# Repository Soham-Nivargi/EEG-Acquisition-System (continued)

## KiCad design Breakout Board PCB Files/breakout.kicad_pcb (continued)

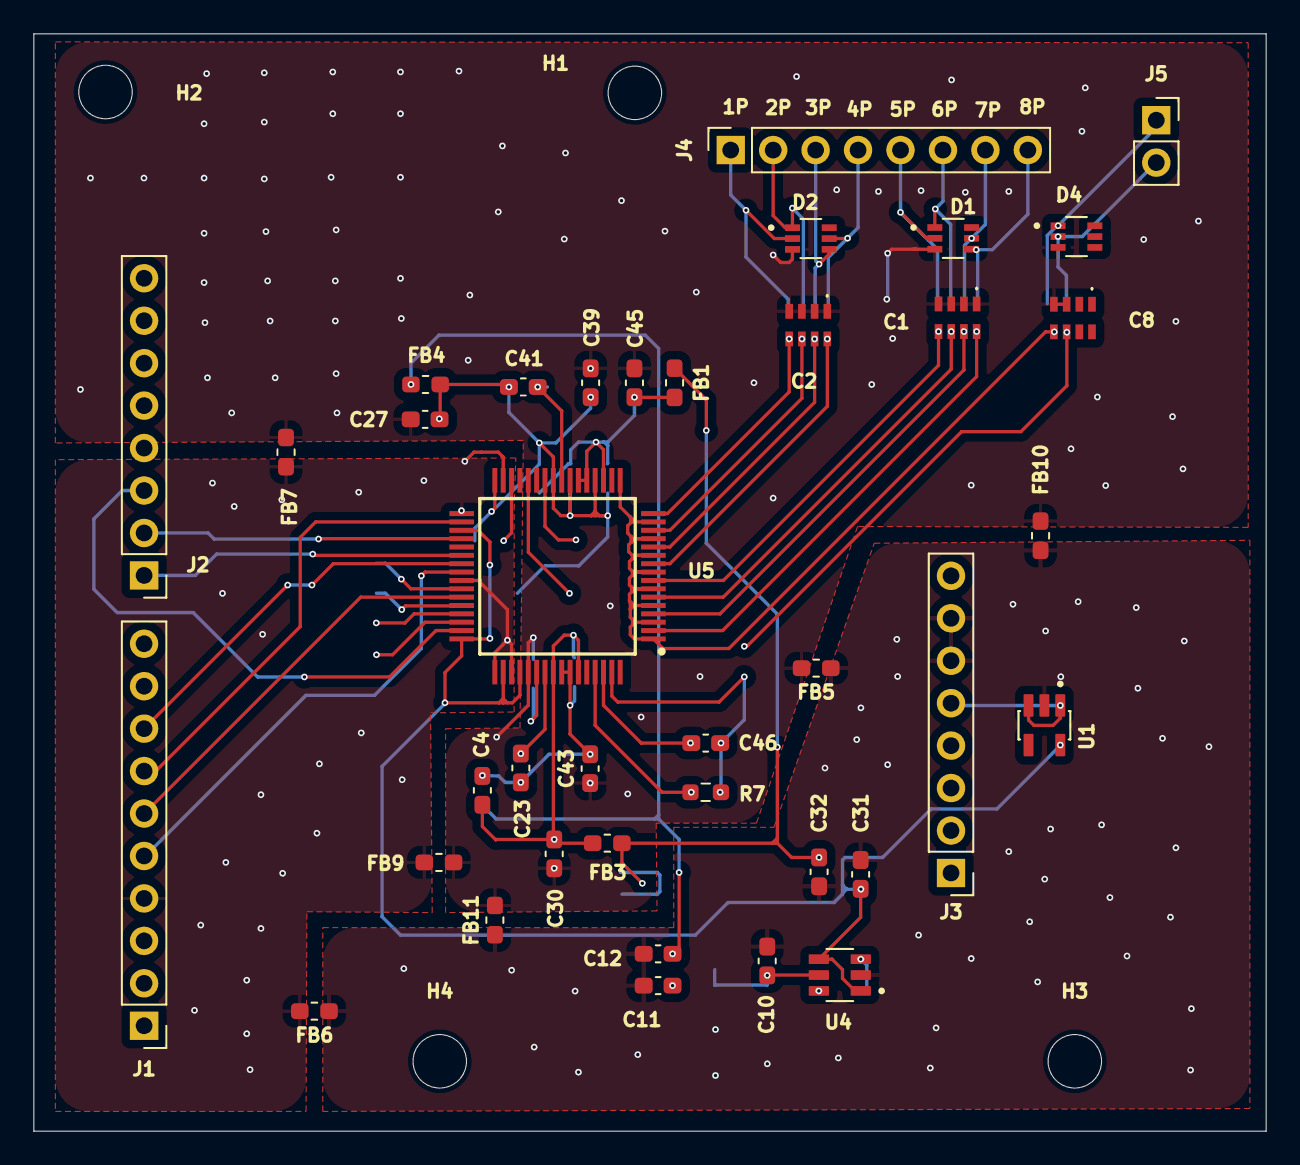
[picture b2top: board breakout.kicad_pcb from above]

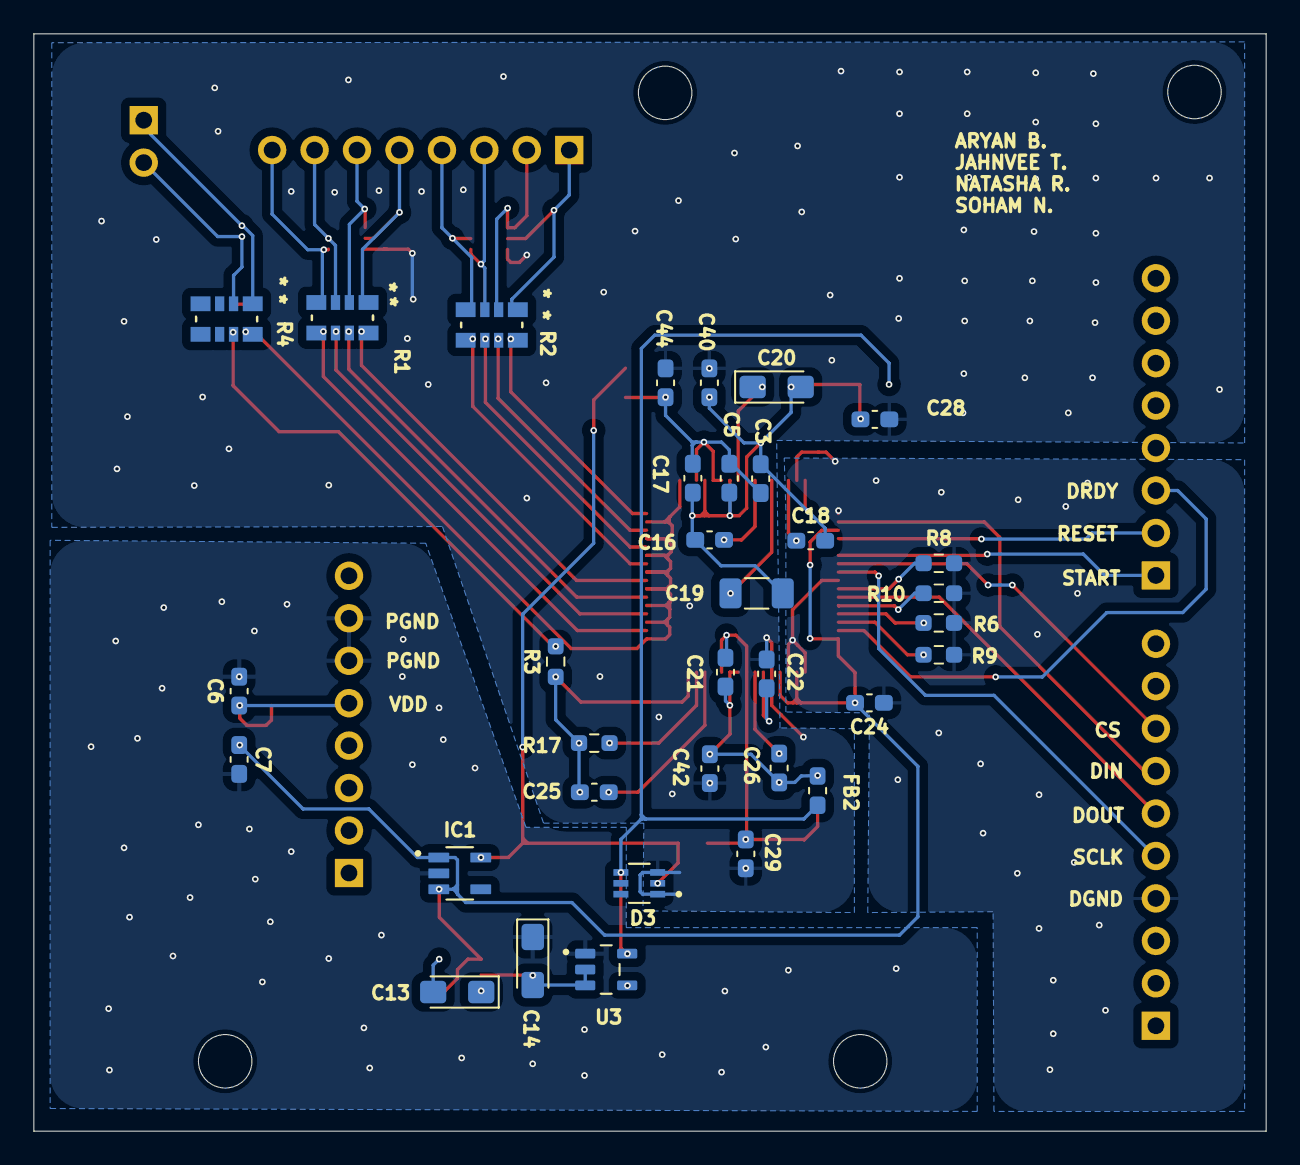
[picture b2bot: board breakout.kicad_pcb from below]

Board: 2 copper layers, 73.7 x 65.7 mm, 76 parts (34 on the bottom side), 55 nets.

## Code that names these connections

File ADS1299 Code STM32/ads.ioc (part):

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Mcu.Name=STM32F103R(8-B)Tx
Mcu.Package=LQFP64
Mcu.UserName=STM32F103RBTx
PA13.GPIOParameters=GPIO_Label
PA13.GPIO_Label=TMS
PA13.Mode=Serial_Wire
PA13.Signal=SYS_JTMS-SWDIO
PA14.GPIOParameters=GPIO_Label
PA14.GPIO_Label=TCK
PA14.Mode=Serial_Wire
PA14.Signal=SYS_JTCK-SWCLK
PA2.GPIOParameters=GPIO_Speed,GPIO_PuPd,GPIO_Label,GPIO_Mode
PA2.GPIO_Label=USART_TX
PA2.GPIO_Mode=GPIO_MODE_AF_PP
PA2.GPIO_PuPd=GPIO_NOPULL
PA2.GPIO_Speed=GPIO_SPEED_FREQ_LOW
PA2.Mode=Asynchronous
PA2.Signal=USART2_TX
PA3.GPIOParameters=GPIO_Speed,GPIO_PuPd,GPIO_Label,GPIO_Mode
PA3.GPIO_Label=USART_RX
PA3.GPIO_Mode=GPIO_MODE_AF_PP
PA3.GPIO_PuPd=GPIO_NOPULL
PA3.GPIO_Speed=GPIO_SPEED_FREQ_LOW
PA3.Mode=Asynchronous
PA3.Signal=USART2_RX
PA5.Mode=Full_Duplex_Master
PA5.Signal=SPI1_SCK
PA6.Mode=Full_Duplex_Master
PA6.Signal=SPI1_MISO
PA7.Mode=Full_Duplex_Master
PA7.Signal=SPI1_MOSI
PA8.Signal=GPIO_Output
PB10.Signal=GPIO_Output
PB3.GPIOParameters=GPIO_Label
PB3.GPIO_Label=SWO
PB3.Signal=SYS_JTDO-TRACESWO
PB4.Signal=GPIO_Input
PB6.Signal=GPIO_Output
PC13-TAMPER-RTC.GPIOParameters=GPIO_PuPd,GPIO_Label
PC13-TAMPER-RTC.GPIO_Label=B1 [Blue PushButton]
PC13-TAMPER-RTC.GPIO_PuPd=GPIO_NOPULL
PC13-TAMPER-RTC.Signal=GPXTI13
PC14-OSC32_IN.Mode=LSE-External-Oscillator
PC14-OSC32_IN.Signal=RCC_OSC32_IN
PC15-OSC32_OUT.Mode=LSE-External-Oscillator
PC15-OSC32_OUT.Signal=RCC_OSC32_OUT
PD0-OSC_IN.Mode=HSE-External-Clock-Source
PD0-OSC_IN.Signal=RCC_OSC_IN
PD1-OSC_OUT.Mode=HSE-External-Clock-Source
PD1-OSC_OUT.Signal=RCC_OSC_OUT
RCC.SYSCLKFreq_VALUE=16000000
RCC.SYSCLKSource=RCC_SYSCLKSOURCE_PLLCLK
board=NUCLEO-F103RB
boardIOC=true

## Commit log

2025-01-26 EEG commit full project
